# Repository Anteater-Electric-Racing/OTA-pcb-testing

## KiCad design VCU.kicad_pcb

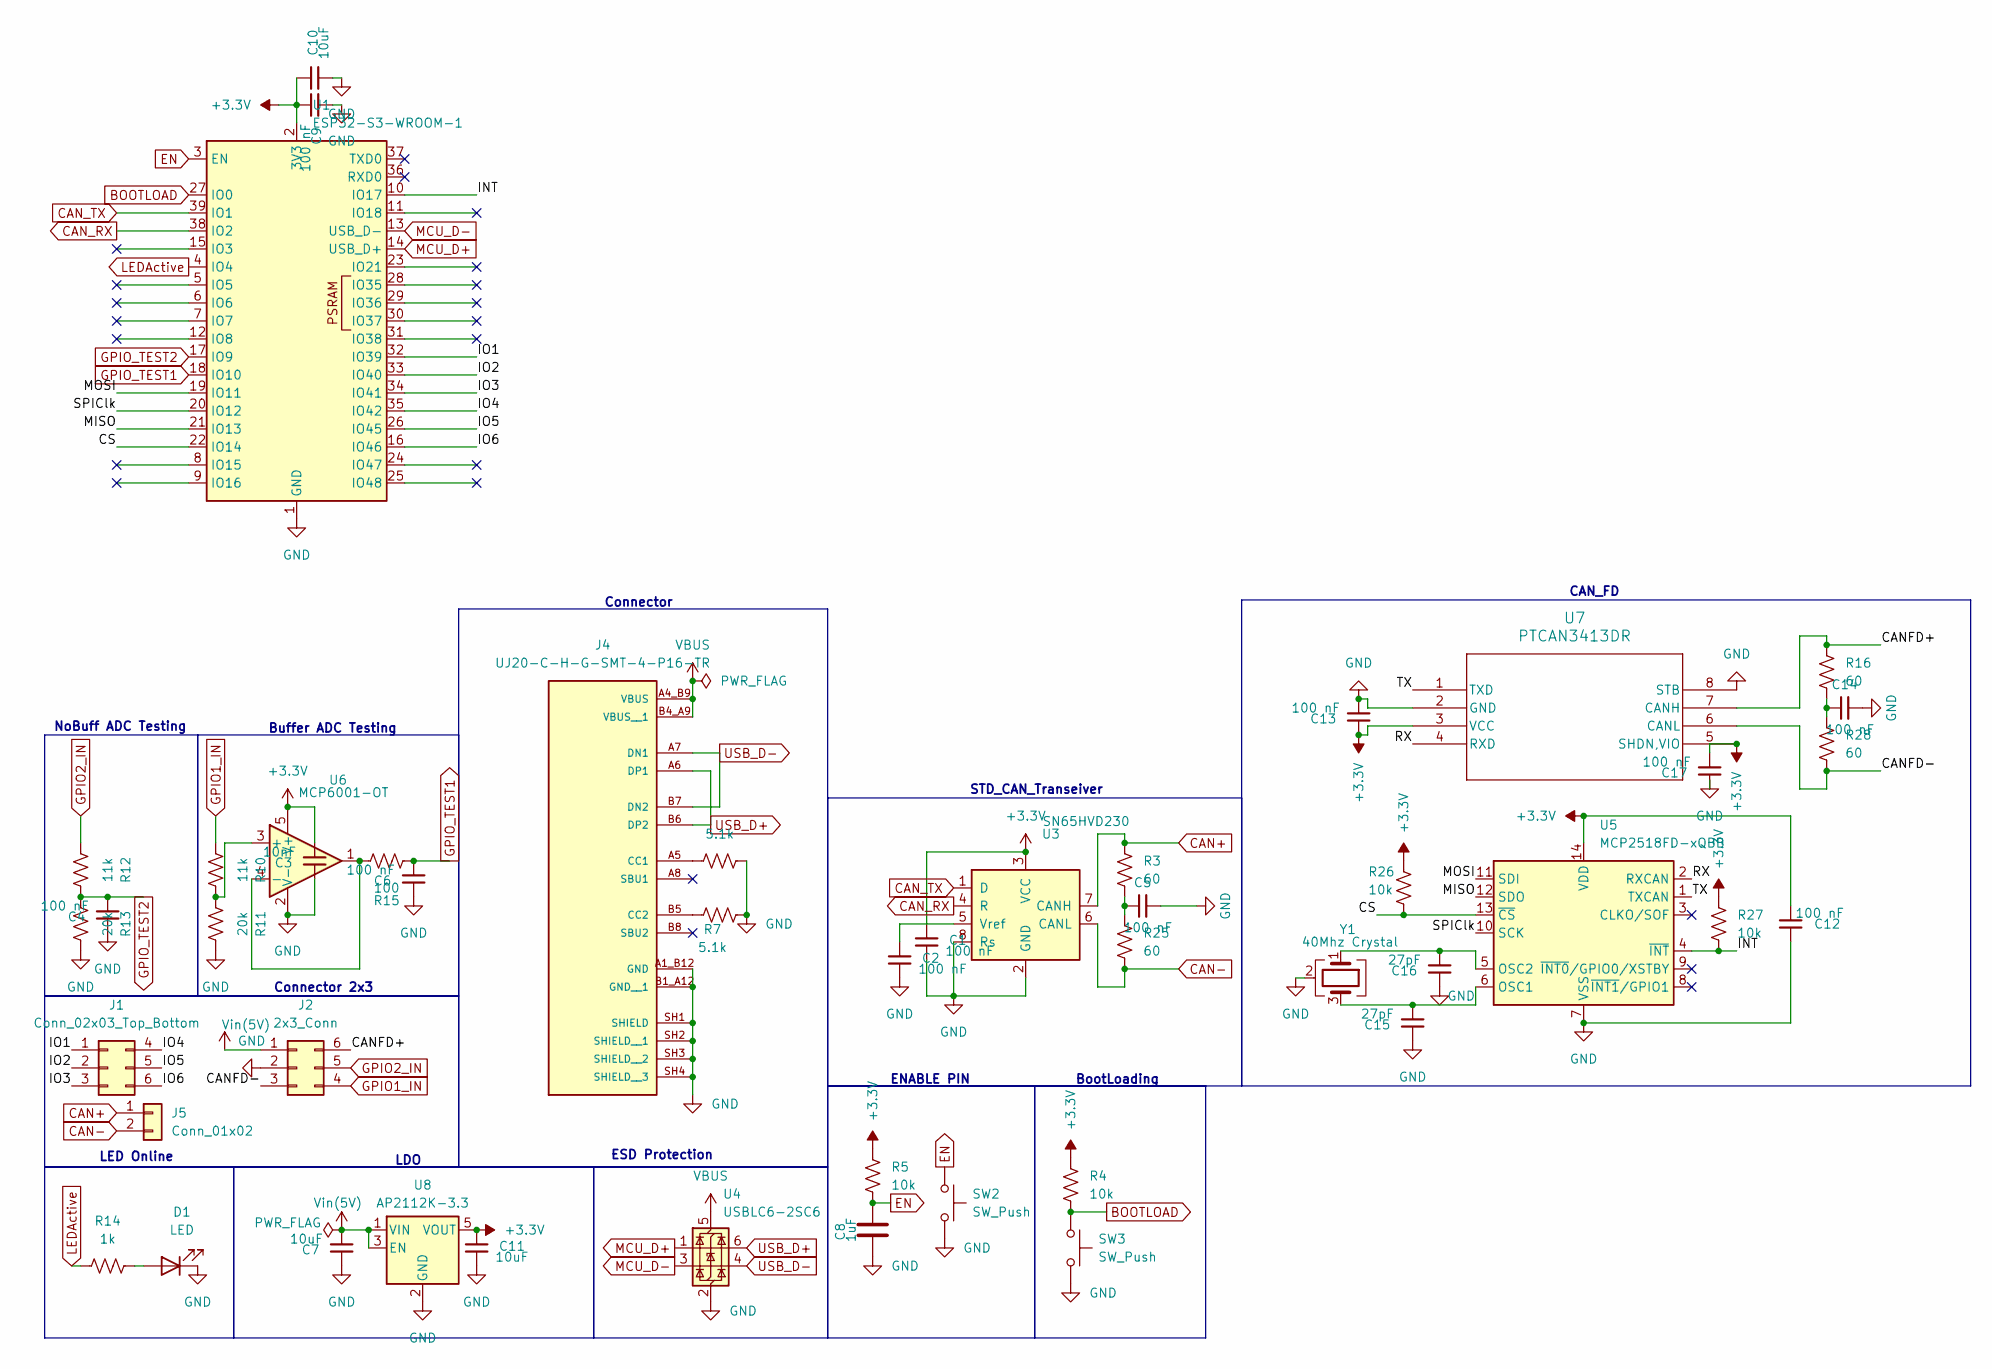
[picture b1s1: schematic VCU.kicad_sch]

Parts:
C1, C2, C4, C5, C6, C9, C12, C13, C14, C17: 100 nF; C_0805_2012Metric
C3: 10nF; C_0805_2012Metric
C7, C10, C11: 10uF; C_0805_2012Metric
C8: 1uF; C_0805_2012Metric
C15, C16: 27pF; C_0805_2012Metric
D1: LED; LED_D4.0mm
J1: Conn_02x03_Top_Bottom; PinHeader_2x03_P2.54mm_Vertical
J2: 2x3_Conn; Molex_Mini-Fit_Jr_5566-06A2_2x03_P4.20mm_Vertical
J4: UJ20-C-H-G-SMT-4-P16-TR; SAMESKY_UJ20-C-H-G-SMT-4-P16-TR; PARTREV 1.0
J5: Conn_01x02; Molex_Mini-Fit_Jr_5566-02A_2x01_P4.20mm_Vertical
R3, R16, R25, R28: 60; R_0805_2012Metric
R4, R5, R26, R27: 10k; R_0805_2012Metric
R6, R7: 5.1k; R_0805_2012Metric
R10, R12: 11k; R_0805_2012Metric
R11, R13: 20k; R_0805_2012Metric
R14: 1k; R_0805_2012Metric
R15: 100; R_0805_2012Metric
SW2, SW3: SW_Push; Button_MJTP1250
U1: ESP32-S3-WROOM-1
U3: SN65HVD230; SOIC-8_3.9x4.9mm_P1.27mm
U4: USBLC6-2SC6; SOT-23-6; LCSC C2827654
U5: MCP2518FD-xQBB; DFN-14-1EP_3x4.5mm_P0.65mm_EP1.65x4.25mm
U6: MCP6001-OT; SOT-23-5
U7: PTCAN3413DR; SOIC8_D_TEX
U8: AP2112K-3.3; SOT-23-5
Y1: 40Mhz Crystal; Crystal_SMD_3225-4Pin_3.2x2.5mm

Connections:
+3.3V: C1.1, C3.2, C9.2, C10.1, C11.1, C12.2, C13.1, C17.2, R4.1, R5.1, R26.1, R27.2, U1.2 (3V3), U3.3 (VCC), U5.14 (VDD), U6.5 (V+), U7.3 (VCC), U7.5 (SHDN,VIO), U8.5 (VOUT)
/CANFD+: J2.6, R16.1, U7.7 (CANH)
/CANFD-: J2.3, R28.2, U7.6 (CANL)
/CS: R26.2, U1.22 (IO14), U5.13 (~CS)
/INT: R27.1, U1.10 (IO17), U5.4 (~INT)
/IO1: J1.1, U1.32 (IO39)
/IO2: J1.2, U1.33 (IO40)
/IO3: J1.3, U1.34 (IO41)
/IO4: J1.4, U1.35 (IO42)
/IO5: J1.5, U1.26 (IO45)
/IO6: J1.6, U1.16 (IO46)
/MISO: U1.21 (IO13), U5.12 (SDO)
/MOSI: U1.19 (IO11), U5.11 (SDI)
/RX: U5.2 (RXCAN), U7.4 (RXD)
/SPIClk: U1.20 (IO12), U5.10 (SCK)
/TX: U5.1 (TXCAN), U7.1 (TXD)
BOOTLOAD: R4.2, SW3.1, U1.27 (IO0); also elsewhere on the board
CAN+: J5.1, R3.1, U3.7 (CANH)
CAN-: J5.2, R25.2, U3.6 (CANL)
CAN_RX: U1.38 (IO2), U3.4 (R)
CAN_TX: U1.39 (IO1), U3.1 (D)
EN: C8.2, R5.2, SW2.1, U1.3 (EN)
GND: C1.2, C2.2, C3.1, C4.1, C5.2, C6.1, C7.1, C8.1, C9.1, C10.2, C11.2, C12.1, C13.2, C14.2, C15.1, C16.1, C17.1, D1.1 (K), J2.2, J4.A1_B12 (GND), J4.B1_A12 (GND__1), J4.SH1 (SHIELD), J4.SH2 (SHIELD__1), J4.SH3 (SHIELD__2), J4.SH4 (SHIELD__3), R6.2, R7.2, R11.2, R13.2, SW2.2, SW3.2, U1.1 (GND), U1.40 (GND), U1.41 (GND), U3.2 (GND), U3.8 (Rs), U4.2 (GND), U5.7 (VSS), U5.15 (VSS), U6.2 (V-), U7.2 (GND), U7.8 (STB), U8.2 (GND), Y1.2 (G), Y1.4 (G); also elsewhere on the board
GPIO1_IN: J2.4, R10.1
GPIO2_IN: J2.5, R12.1
GPIO_TEST1: C6.2, R15.1, U1.18 (IO10)
GPIO_TEST2: C4.2, R12.2, R13.1, U1.17 (IO9)
LEDActive: R14.1, U1.4 (IO4)
MCU_D+: U1.14 (USB_D+), U4.1 (I/O1)
MCU_D-: U1.13 (USB_D-), U4.3 (I/O2)
unnamed: C5.1, R3.2, R25.1
unnamed: C14.1, R16.2, R28.1
unnamed: D1.2 (A), R14.2
unnamed: J4.A5 (CC1), R6.1
unnamed: J4.B5 (CC2), R7.1
unnamed: C2.1, U3.5 (Vref)
unnamed: C15.2, U5.6 (OSC1), Y1.3
unnamed: C16.2, U5.5 (OSC2), Y1.1
unnamed: R10.2, R11.1, U6.3 (+)
unnamed: R15.2, U6.1, U6.4 (-)
USB_D+: J4.A6 (DP1), J4.B6 (DP2), U4.6 (I/O1)
USB_D-: J4.A7 (DN1), J4.B7 (DN2), U4.4 (I/O2)
VBUS: J4.A4_B9 (VBUS), J4.B4_A9 (VBUS__1), U4.5 (VBUS)
Vin(5V): C7.2, J2.1, U8.1 (VIN), U8.3 (EN)

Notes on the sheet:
Connector 2x3
CAN_FD
Buffer ADC Testing
NoBuff ADC Testing
ESD Protection
LDO
STD_CAN_Transeiver
BootLoading
ENABLE PIN
LED Online
Connector

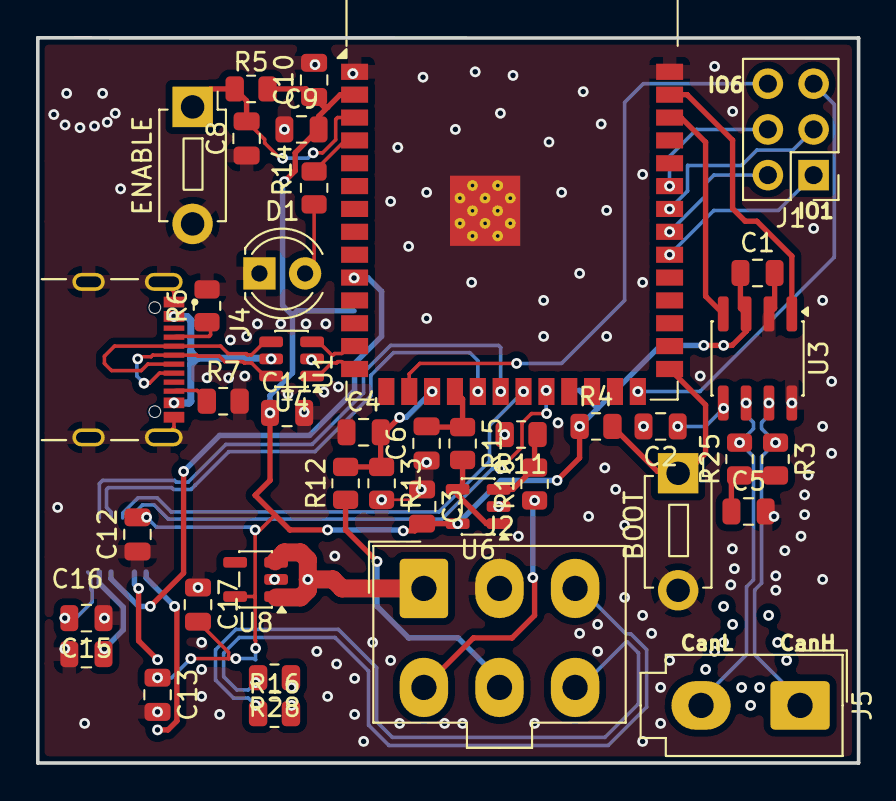
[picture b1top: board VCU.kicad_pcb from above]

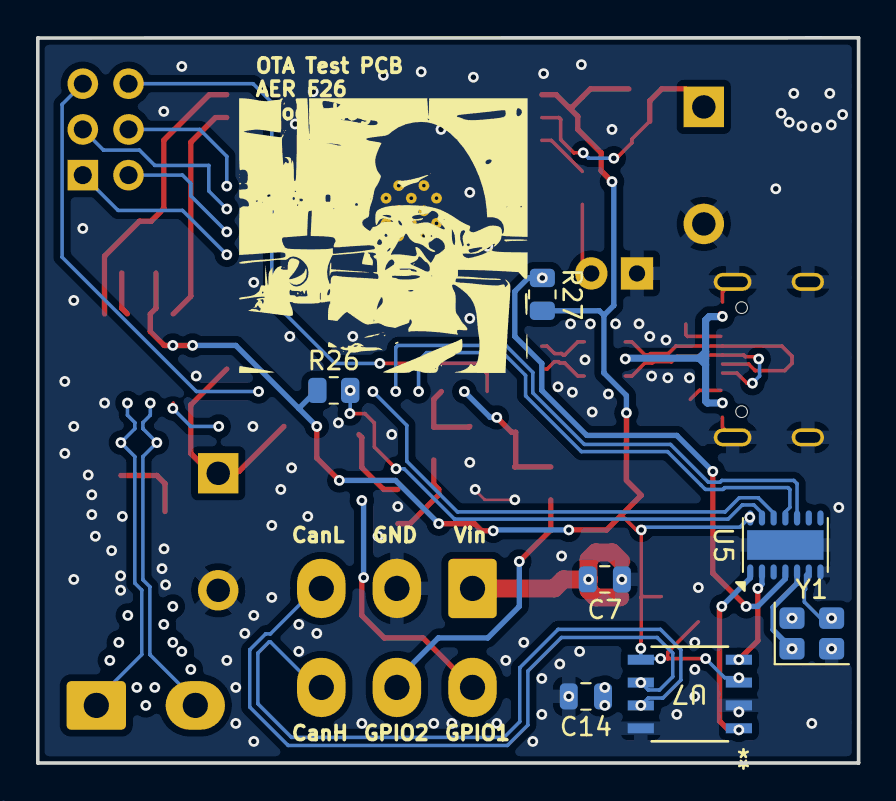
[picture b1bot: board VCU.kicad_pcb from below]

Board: 2 copper layers, 45.6 x 40.3 mm, 48 parts (7 on the bottom side), 44 nets.

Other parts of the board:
BOOT: SW_Push; Button_MJTP1250

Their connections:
BOOTLOAD: BOOT.1; also elsewhere on the board
GND: BOOT.2; also elsewhere on the board
